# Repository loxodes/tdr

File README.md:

# tdr
Prototype time domain reflectometer/sampling oscilloscope.
90 gigasamples/second equivalent time sampling with an actual sampling rate of 5 kilosamples/second.

The input bandwidth is TBD, maybe 8 GHz?

Following is sampling the falling edge of the TDR pulse, impedance of a BNC tee, and a 1.2 GHz sine wave with analog triggering.

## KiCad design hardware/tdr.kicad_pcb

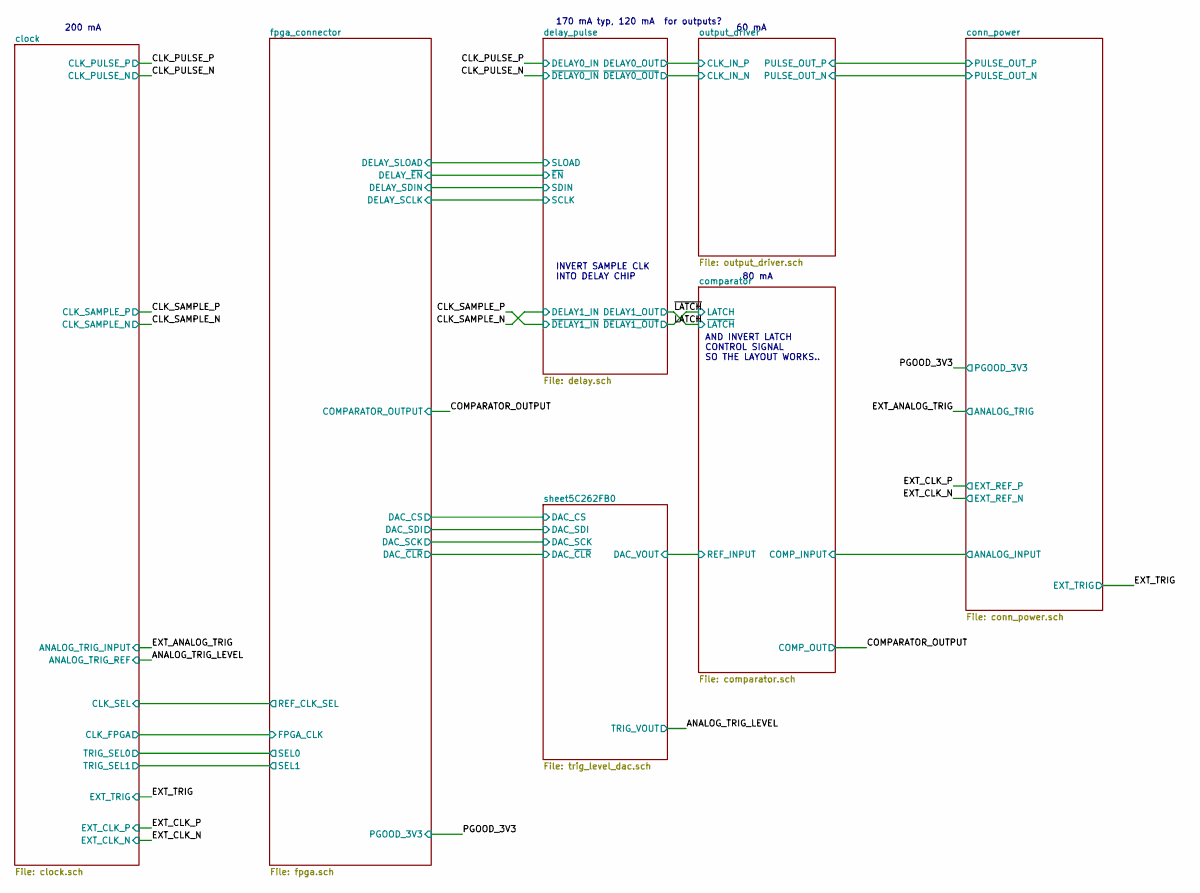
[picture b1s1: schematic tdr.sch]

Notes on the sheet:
200 mA
170 mA typ, 120 mA for outputs?
60 mA
80 mA
INVERT SAMPLE CLK INTO DELAY CHIP
AND INVERT LATCH CONTROL SIGNAL SO THE LAYOUT WORKS..

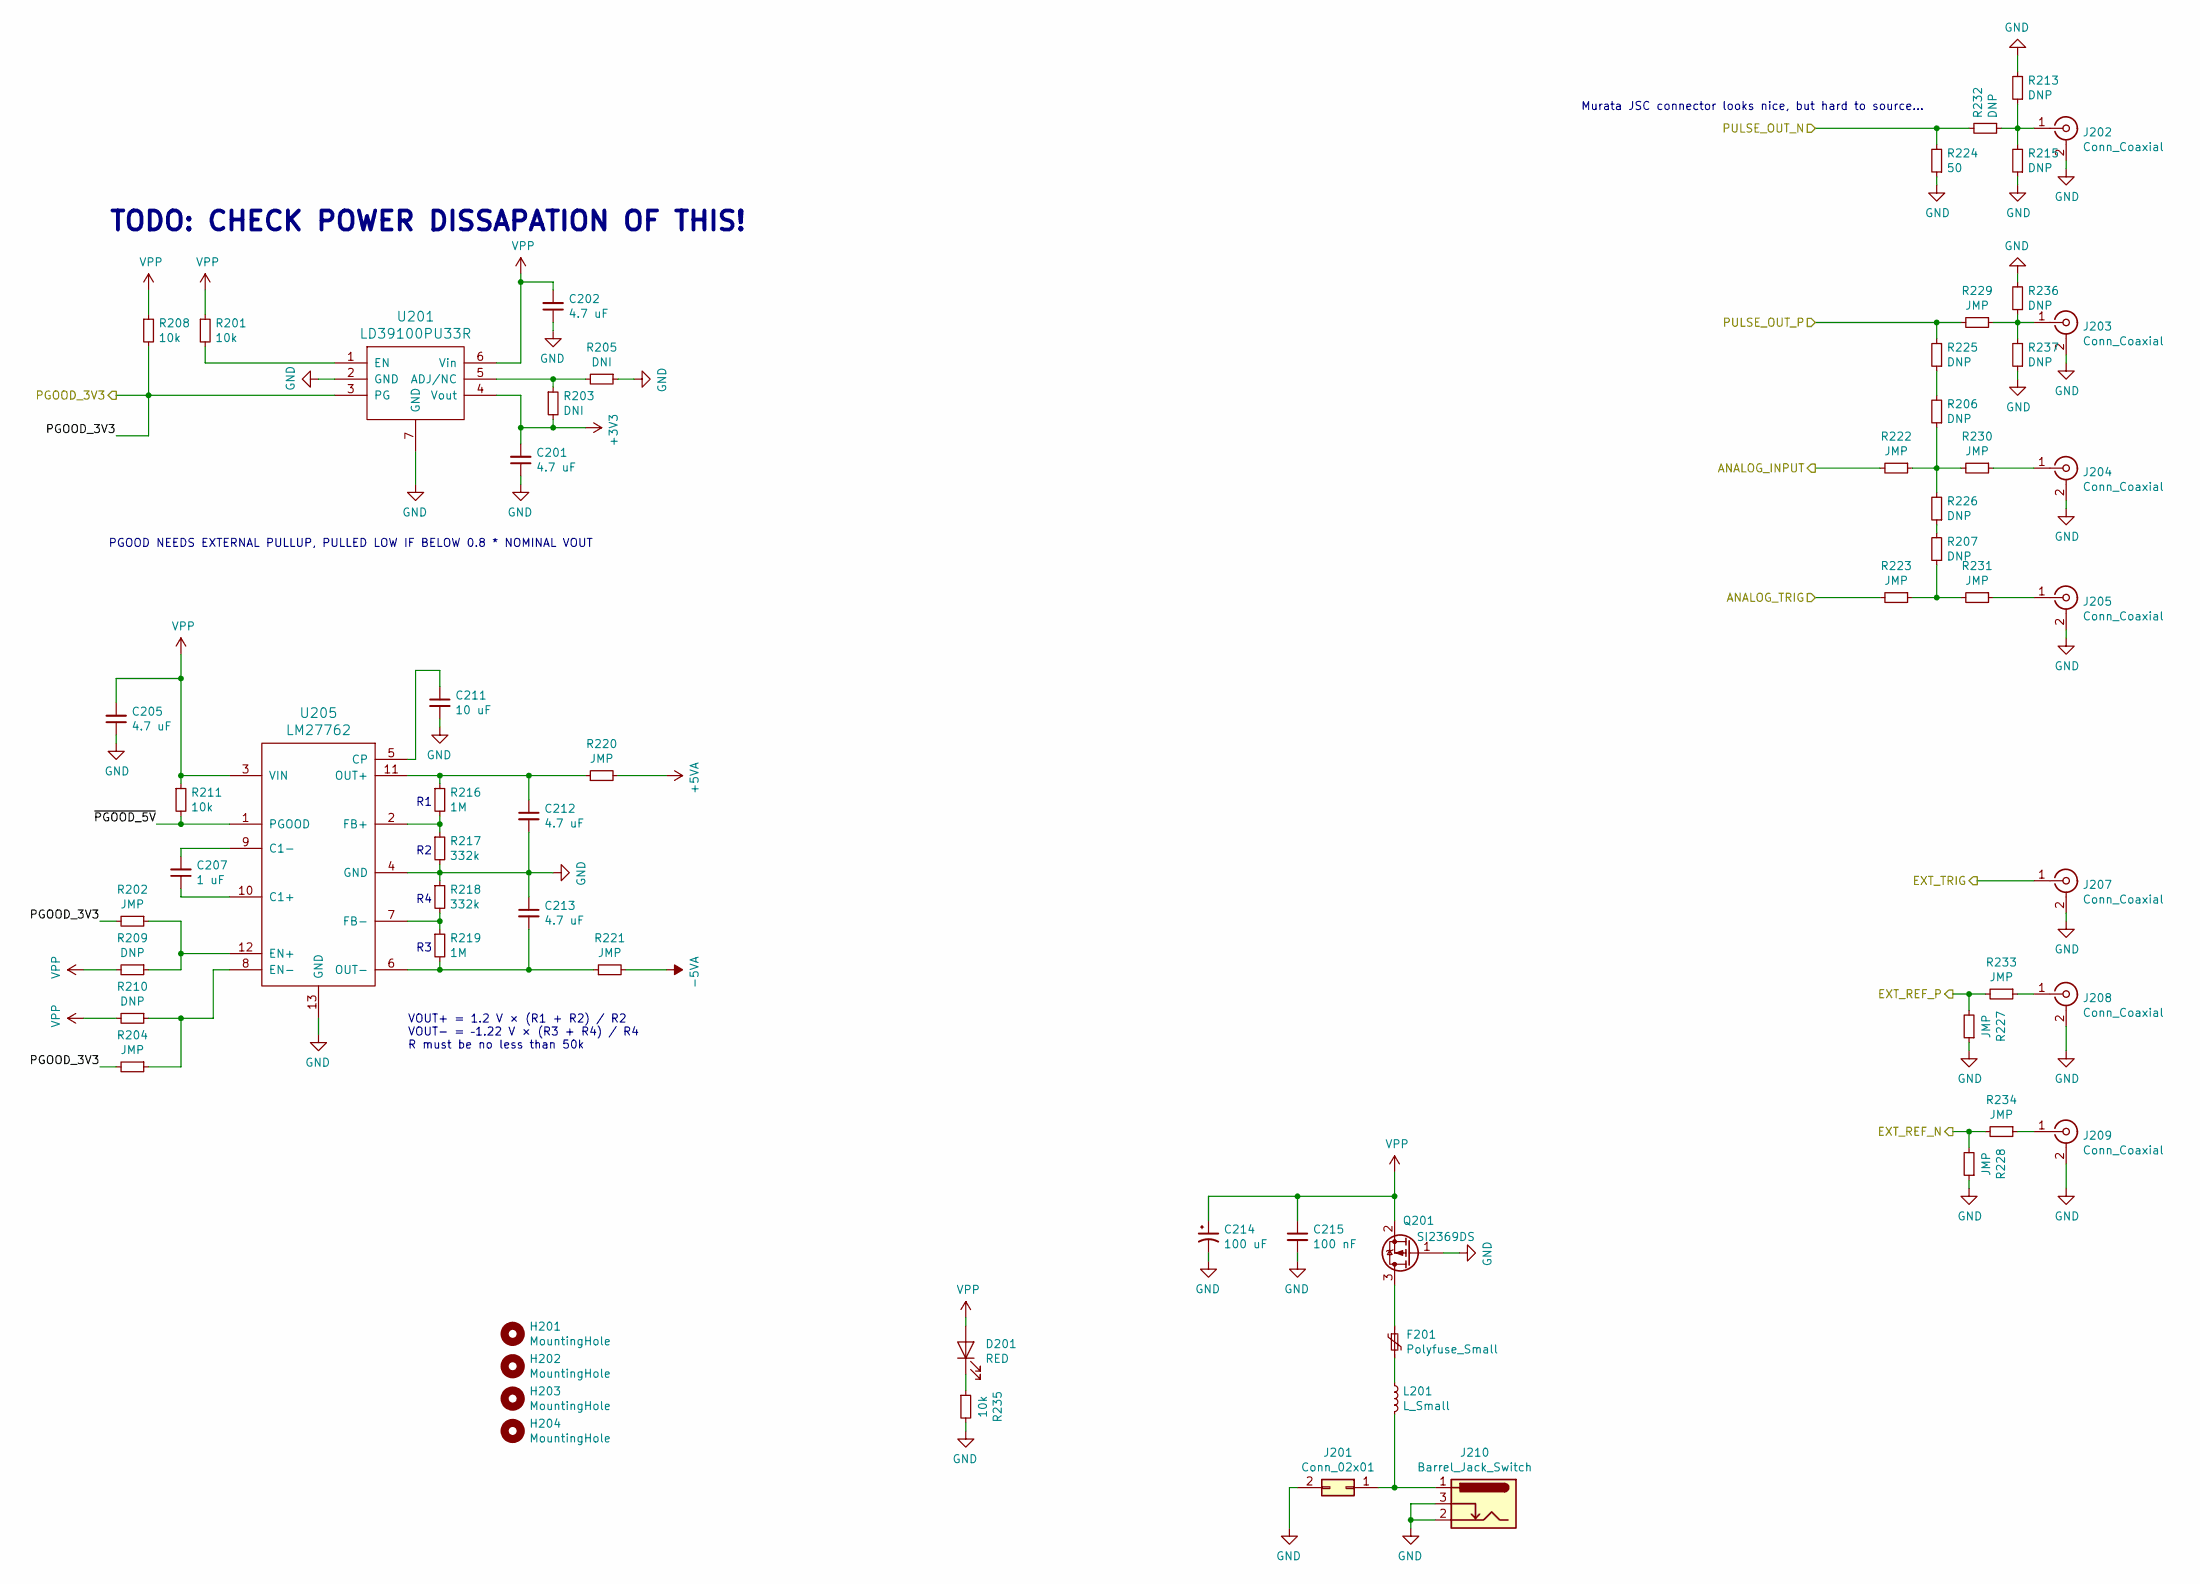
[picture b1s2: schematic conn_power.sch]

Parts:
C201, C202, C205, C212, C213: 4.7 uF; C_0603
C207: 1 uF; C_0402
C211: 10 uF; C_0603
C214: 100 uF; c_elec_6.3x5.8
C215: 100 nF; C_0402
D201: RED; LED_0603
F201: Polyfuse_Small; R_1210
H201, H202, H203, H204: MountingHole; MountingHole_2-5mm
J201: Conn_02x01; TerminalBlock_Pheonix_MPT-2.54mm_2pol
J202: Conn_Coaxial; 734120110_ufl_umc
J203, J204, J205, J207: Conn_Coaxial; SF2921-61345
J208, J209: Conn_Coaxial; 732511150_sma_thin_twopin
J210: Barrel_Jack_Switch; BARREL_JACK
L201: L_Small; R_1210
Q201: SI2369DS; SOT-23
R201, R208, R211, R235: 10k; R_0402
R202, R204, R220, R221, R227, R228, R233, R234: JMP; R_0402
R203, R205: DNI; R_0402
R206, R207, R225, R226, R232: DNP; R_0201
R209, R210, R213, R215, R236, R237: DNP; R_0402
R216, R219: 1M; R_0402
R217, R218: 332k; R_0402
R222, R223, R229, R230, R231: JMP; R_0201
R224: 50; R_0402
U201: LD39100PU33R; DFN-6-1EP_3x3mm_Pitch0.95mm
U205: LM27762; WSON-12-1EP_3x2mm_Pitch0.5mm

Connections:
+3V3: C201.2, R203.2, U201.4 (Vout); also elsewhere on the board
+5VA: R220.2; also elsewhere on the board
-5VA: R221.2; also elsewhere on the board
/EXT_ANALOG_TRIG: R223.2; also elsewhere on the board
/EXT_CLK_N: R228.2, R234.2; also elsewhere on the board
/EXT_CLK_P: R227.2, R233.2; also elsewhere on the board
/EXT_TRIG: J207.1 (In); also elsewhere on the board
/PGOOD_3V3: R202.2, R204.2, R208.2, U201.3 (PG); also elsewhere on the board
/conn_power/ANALOG_INPUT: R222.2; also elsewhere on the board
/conn_power/PULSE_OUT_N: R224.2, R232.2; also elsewhere on the board
/conn_power/PULSE_OUT_P: R225.2, R229.2; also elsewhere on the board
/conn_power/~PGOOD_5V: R211.2, U205.1 (PGOOD)
GND: C201.1, C202.1, C205.1, C211.2, C212.2, C213.1, C214.2, C215.2, J201.2, J202.2 (Ext), J203.2 (Ext), J204.2 (Ext), J205.2 (Ext), J207.2 (Ext), J208.2 (Ext), J209.2 (Ext), J210.2, J210.3, Q201.1 (G), R205.1, R213.2, R215.1, R217.2, R218.1, R224.1, R227.1, R228.1, R235.2, R236.2, R237.1, U201.2 (GND), U201.7 (GND), U205.4 (GND), U205.13 (GND); also elsewhere on the board
unnamed: C207.1, U205.10 (C1+)
unnamed: C207.2, U205.9 (C1-)
unnamed: C211.1, U205.5 (CP)
unnamed: C212.1, R216.1, R220.1, U205.11 (OUT+)
unnamed: C213.2, R219.2, R221.1, U205.6 (OUT-)
unnamed: D201.1 (K), R235.1
unnamed: F201.1, Q201.3 (D)
unnamed: F201.2, L201.1
unnamed: J201.1, J210.1, L201.2
unnamed: J202.1 (In), R213.1, R215.2, R232.1
unnamed: J203.1 (In), R229.1, R236.1, R237.2
unnamed: J204.1 (In), R230.1
unnamed: J205.1 (In), R231.1
unnamed: J208.1 (In), R233.1
unnamed: J209.1 (In), R234.1
unnamed: R201.2, U201.1 (EN)
unnamed: R202.1, R209.1, U205.12 (EN+)
unnamed: R203.1, R205.2, U201.5 (ADJ/NC)
unnamed: R204.1, R210.1, U205.8 (EN-)
unnamed: R206.1, R222.1, R226.2, R230.2
unnamed: R206.2, R225.1
unnamed: R207.1, R223.1, R231.2
unnamed: R207.2, R226.1
unnamed: R216.2, R217.1, U205.2 (FB+)
unnamed: R218.2, R219.1, U205.7 (FB-)
VPP: C202.2, C205.2, C214.1, C215.1, D201.2 (A), Q201.2 (S), R201.1, R208.1, R209.2, R210.2, R211.1, U201.6 (Vin), U205.3 (VIN)

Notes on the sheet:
PGOOD NEEDS EXTERNAL PULLUP, PULLED LOW IF BELOW 0.8 * NOMINAL VOUT
TODO: CHECK POWER DISSAPATION OF THIS!
Murata JSC connector looks nice, but hard to source...
VOUT+ = 1.2 V × (R1 + R2) / R2 VOUT- = –1.22 V × (R3 + R4) / R4 R must be no less than 50k

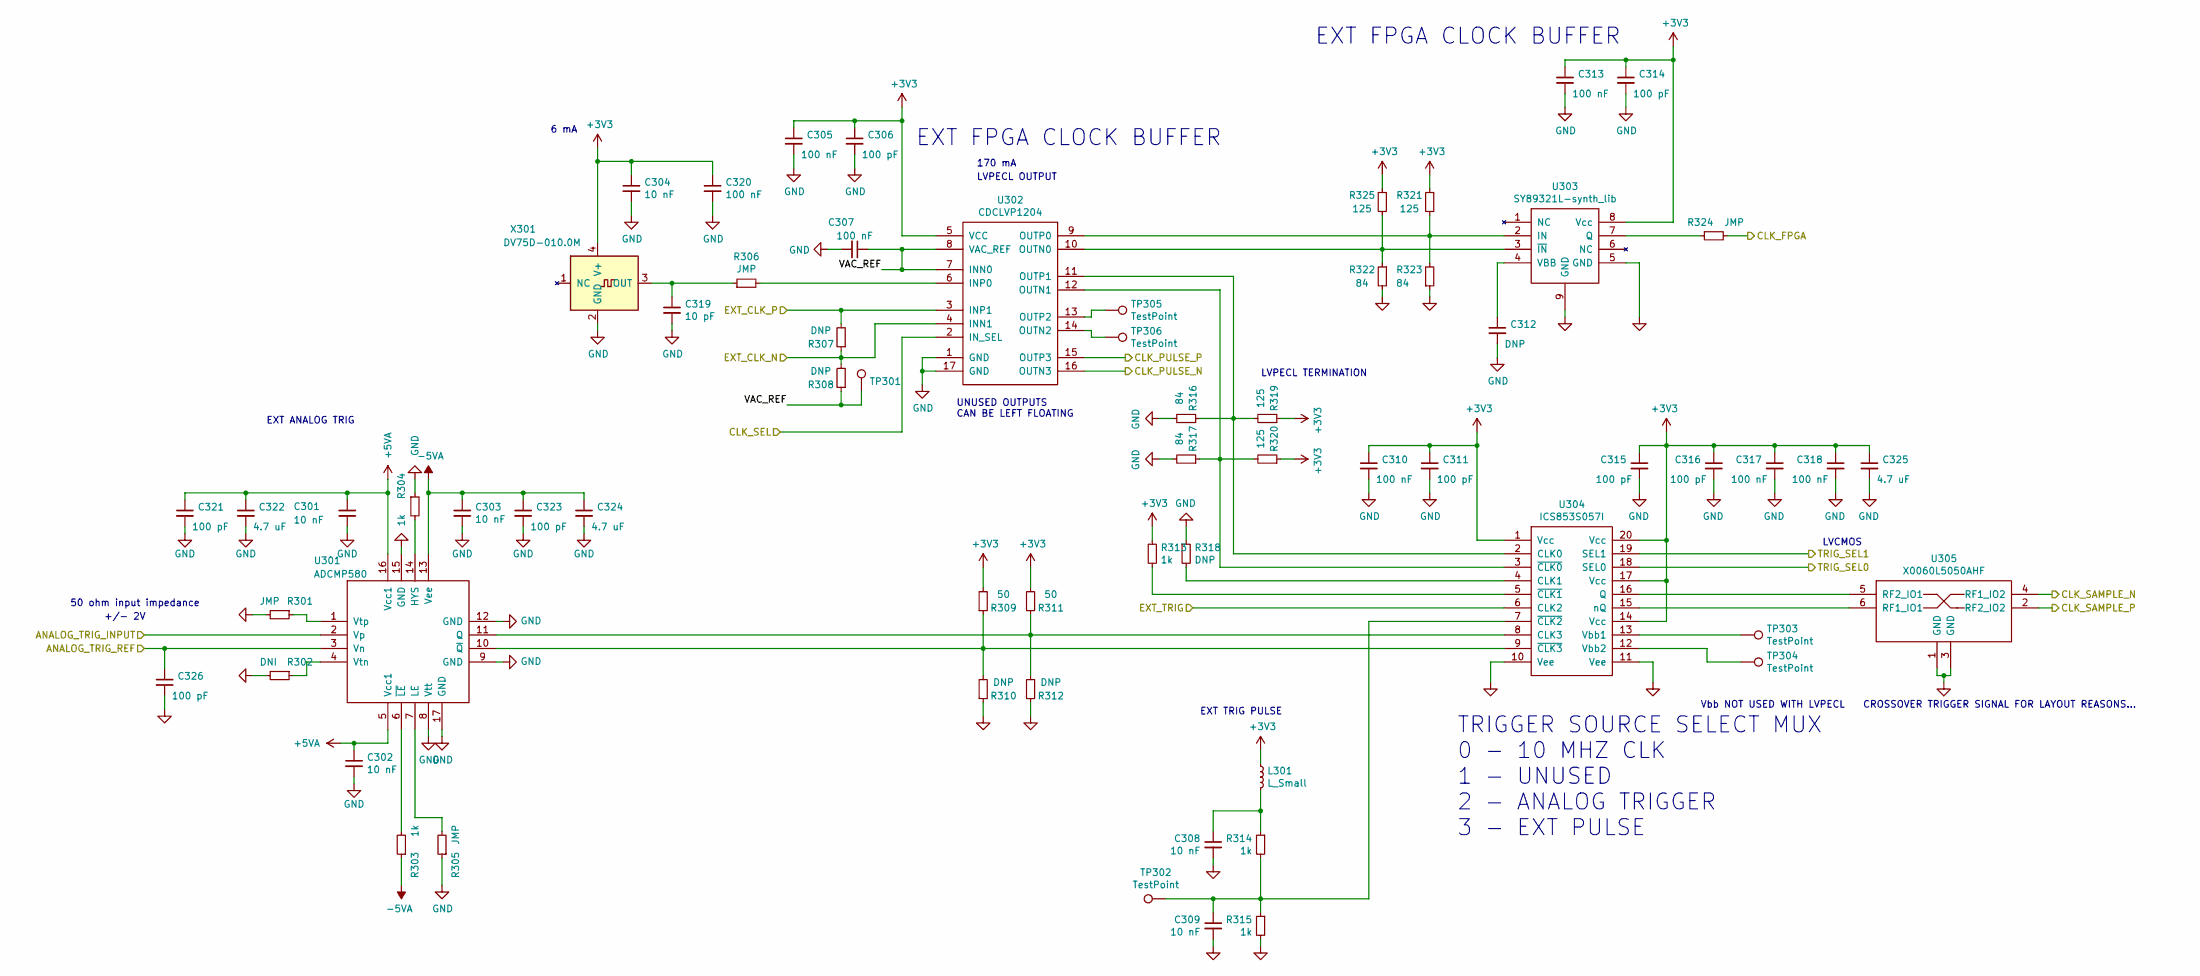
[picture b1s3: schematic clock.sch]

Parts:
C301, C302, C303, C304, C308, C309: 10 nF; C_0402
C305, C307, C310, C313, C317, C318, C320: 100 nF; C_0402
C306, C311, C314, C315, C316, C321, C323, C326: 100 pF; C_0402
C312: DNP; C_0402
C319: 10 pF; C_0402
C322, C324, C325: 4.7 uF; C_0603
L301: L_Small; R_0402
R301, R305, R306, R324: JMP; R_0402
R302: DNI; R_0402
R303, R304, R313, R314, R315: 1k; R_0402
R307, R308, R310, R312, R318: DNP; R_0402
R309, R311: 50; R_0402
R316, R317, R322, R323: 84; R_0402
R319, R320, R321, R325: 125; R_0402
TP301, TP302, TP303, TP304, TP305, TP306: TestPoint; TP07R
U301: ADCMP580; UQFN-16-1EP_3x3mm_Pitch0.5mm
U302: CDCLVP1204; UQFN-16-1EP_3x3mm_Pitch0.5mm
U303: SY89321L-synth_lib; DFN-8-1EP_2x2mm_Pitch0.5mm
U304: ICS853S057I; TSSOP-20_4.4x6.5mm_Pitch0.65mm
U305: X0060L5050AHF
X301: DV75D-010.0M; DV75D

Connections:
+3V3: C304.1, C305.1, C306.1, C310.1, C311.1, C313.1, C314.1, C315.1, C316.1, C317.1, C318.1, C320.1, C325.1, L301.1, R309.2, R311.2, R313.1, R319.1, R320.1, R321.1, R325.1, U302.5 (VCC), U303.8 (Vcc), U304.1 (Vcc), U304.14 (Vcc), U304.17 (Vcc), U304.20 (Vcc), X301.4 (V+); also elsewhere on the board
+5VA: C301.1, C302.1, C321.1, C322.1, U301.5 (Vcc1), U301.16 (Vcc1); also elsewhere on the board
-5VA: C303.1, C323.1, C324.1, R303.1, U301.13 (Vee); also elsewhere on the board
/ANALOG_TRIG_LEVEL: C326.1, U301.3 (Vn); also elsewhere on the board
/CLK_PULSE_N: U302.16 (OUTN3); also elsewhere on the board
/CLK_PULSE_P: U302.15 (OUTP3); also elsewhere on the board
/CLK_SAMPLE_N: U305.4 (RF1_IO2); also elsewhere on the board
/CLK_SAMPLE_P: U305.2 (RF2_IO2); also elsewhere on the board
/EXT_ANALOG_TRIG: U301.2 (Vp); also elsewhere on the board
/EXT_CLK_N: R307.1, R308.2, U302.4 (INN1); also elsewhere on the board
/EXT_CLK_P: R307.2, U302.3 (INP1); also elsewhere on the board
/EXT_TRIG: U304.6 (CLK2); also elsewhere on the board
/clock/CLK_FPGA: R324.2; also elsewhere on the board
/clock/CLK_SEL: U302.2 (IN_SEL); also elsewhere on the board
/clock/VAC_REF: C307.1, R308.1, TP301.1, U302.7 (INN0), U302.8 (VAC_REF)
/fpga_connector/SEL0: U304.18 (SEL0); also elsewhere on the board
/fpga_connector/SEL1: U304.19 (SEL1); also elsewhere on the board
GND: C301.2, C302.2, C303.2, C304.2, C305.2, C306.2, C307.2, C308.2, C309.2, C310.2, C311.2, C312.2, C313.2, C314.2, C315.2, C316.2, C317.2, C318.2, C319.2, C320.2, C321.2, C322.2, C323.2, C324.2, C325.2, C326.2, R301.2, R302.2, R304.1, R305.1, R310.1, R312.1, R315.2, R316.2, R317.2, R318.1, R322.2, R323.1, U301.8 (Vtt), U301.9 (GND), U301.12 (GND), U301.15 (GND), U301.17 (GND), U302.1 (GND), U302.17 (GND), U303.5 (GND), U303.9 (GND), U304.10 (Vee), U304.11 (Vee), U305.1 (GND), U305.3 (GND), X301.2 (GND); also elsewhere on the board
unnamed: C308.1, L301.2, R314.1
unnamed: C309.1, R314.2, R315.1, TP302.1, U304.7 (~CLK2)
unnamed: C312.1, U303.4 (VBB)
unnamed: C319.1, R306.1, X301.3 (OUT)
unnamed: R301.1, U301.1 (Vtp)
unnamed: R302.1, U301.4 (Vtn)
unnamed: R303.2, U301.6 (~LE)
unnamed: R304.2, U301.14 (HYS)
unnamed: R305.2, U301.7 (LE)
unnamed: R306.2, U302.6 (INP0)
unnamed: R309.1, R310.2, U301.10 (~Q), U304.9 (~CLK3)
unnamed: R311.1, R312.2, U301.11 (Q), U304.8 (CLK3)
unnamed: R313.2, U304.5 (~CLK1)
unnamed: R316.1, R319.2, U302.11 (OUTP1), U304.2 (CLK0)
unnamed: R317.1, R320.2, U302.12 (OUTN1), U304.3 (~CLK0)
unnamed: R318.2, U304.4 (CLK1)
unnamed: R321.2, R323.2, U302.9 (OUTP0), U303.2 (IN)
unnamed: R322.1, R325.2, U302.10 (OUTN0), U303.3 (~IN)
unnamed: R324.1, U303.7 (Q)
unnamed: TP303.1, U304.13 (Vbb1)
unnamed: TP304.1, U304.12 (Vbb2)
unnamed: TP305.1, U302.13 (OUTP2)
unnamed: TP306.1, U302.14 (OUTN2)
unnamed: U304.15 (nQ), U305.6 (RF1_IO1)
unnamed: U304.16 (Q), U305.5 (RF2_IO1)

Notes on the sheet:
6 mA
170 mA
LVPECL OUTPUT
EXT ANALOG TRIG
LVPECL TERMINATION
+/- 2V
EXT TRIG PULSE
50 ohm input impedance
LVCMOS
Vbb NOT USED WITH LVPECL
TRIGGER SOURCE SELECT MUX 0 - 10 MHZ CLK 1 - UNUSED 2 - ANALOG TRIGGER 3 - EXT PULSE
EXT FPGA CLOCK BUFFER
UNUSED OUTPUTS CAN BE LEFT FLOATING
CROSSOVER TRIGGER SIGNAL FOR LAYOUT REASONS...

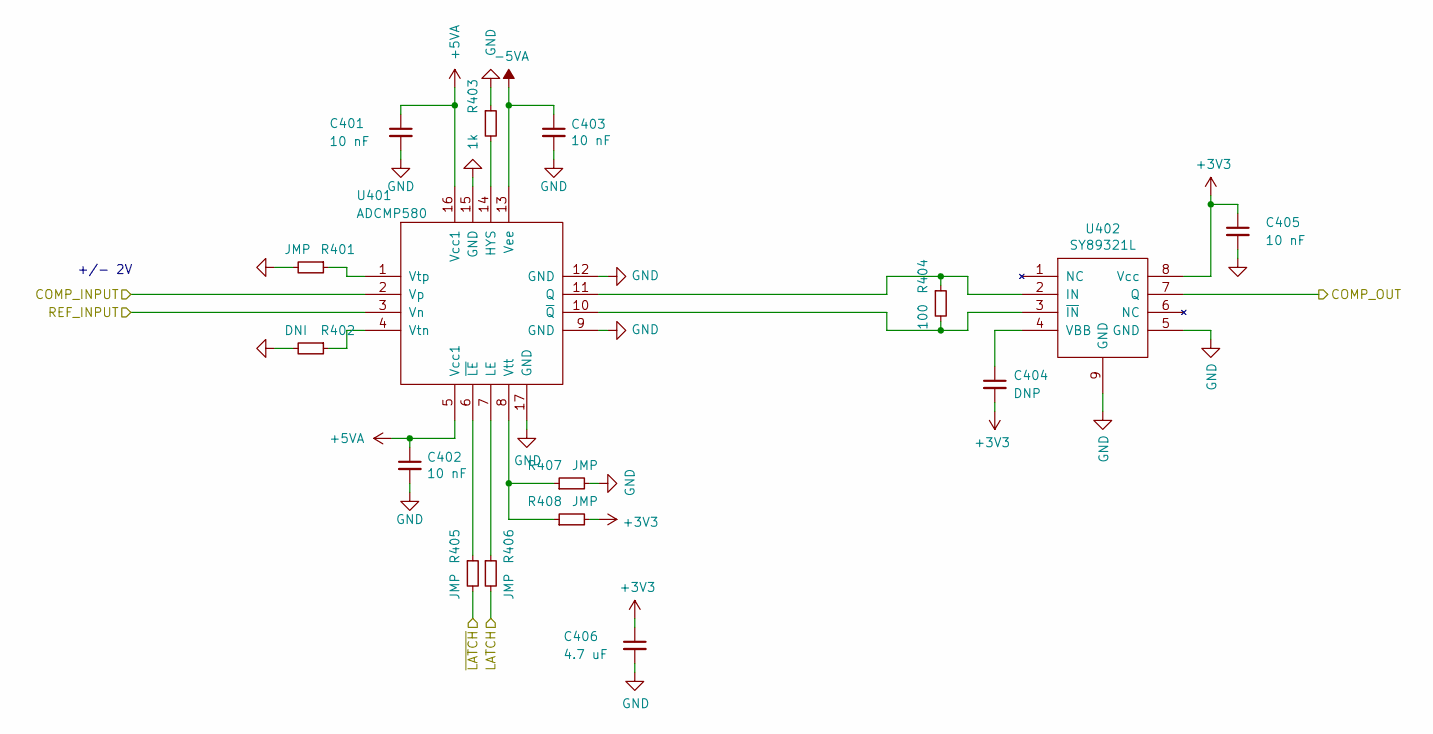
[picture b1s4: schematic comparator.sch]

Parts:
C401, C402, C403, C405: 10 nF; C_0402
C404: DNP; C_0402
C406: 4.7 uF; C_0603
R401, R405, R406, R407, R408: JMP; R_0402
R402: DNI; R_0402
R403: 1k; R_0402
R404: 100; R_0402
U401: ADCMP580; QFN-16-1EP_3x3mm_Pitch0.5mm
U402: SY89321L; DFN-8-1EP_2x2mm_Pitch0.5mm

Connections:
+3V3: C404.2, C405.1, C406.1, R408.2, U402.8 (Vcc); also elsewhere on the board
+5VA: C401.1, C402.1, U401.5 (Vcc1), U401.16 (Vcc1); also elsewhere on the board
-5VA: C403.1, U401.13 (Vee); also elsewhere on the board
/COMPARATOR_OUTPUT: U402.7 (Q); also elsewhere on the board
/LATCH: R406.2; also elsewhere on the board
/conn_power/ANALOG_INPUT: U401.2 (Vp); also elsewhere on the board
/sheet5C262FB0/DAC_VOUT: U401.3 (Vn); also elsewhere on the board
/~LATCH: R405.2; also elsewhere on the board
GND: C401.2, C402.2, C403.2, C405.2, C406.2, R401.2, R402.2, R403.1, R407.2, U401.9 (GND), U401.12 (GND), U401.15 (GND), U401.17 (GND), U402.5 (GND), U402.9 (GND); also elsewhere on the board
unnamed: C404.1, U402.4 (VBB)
unnamed: R401.1, U401.1 (Vtp)
unnamed: R402.1, U401.4 (Vtn)
unnamed: R403.2, U401.14 (HYS)
unnamed: R404.1, U401.11 (Q), U402.2 (IN)
unnamed: R404.2, U401.10 (~Q), U402.3 (~IN)
unnamed: R405.1, U401.6 (~LE)
unnamed: R406.1, U401.7 (LE)
unnamed: R407.1, R408.1, U401.8 (Vtt)

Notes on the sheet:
+/- 2V

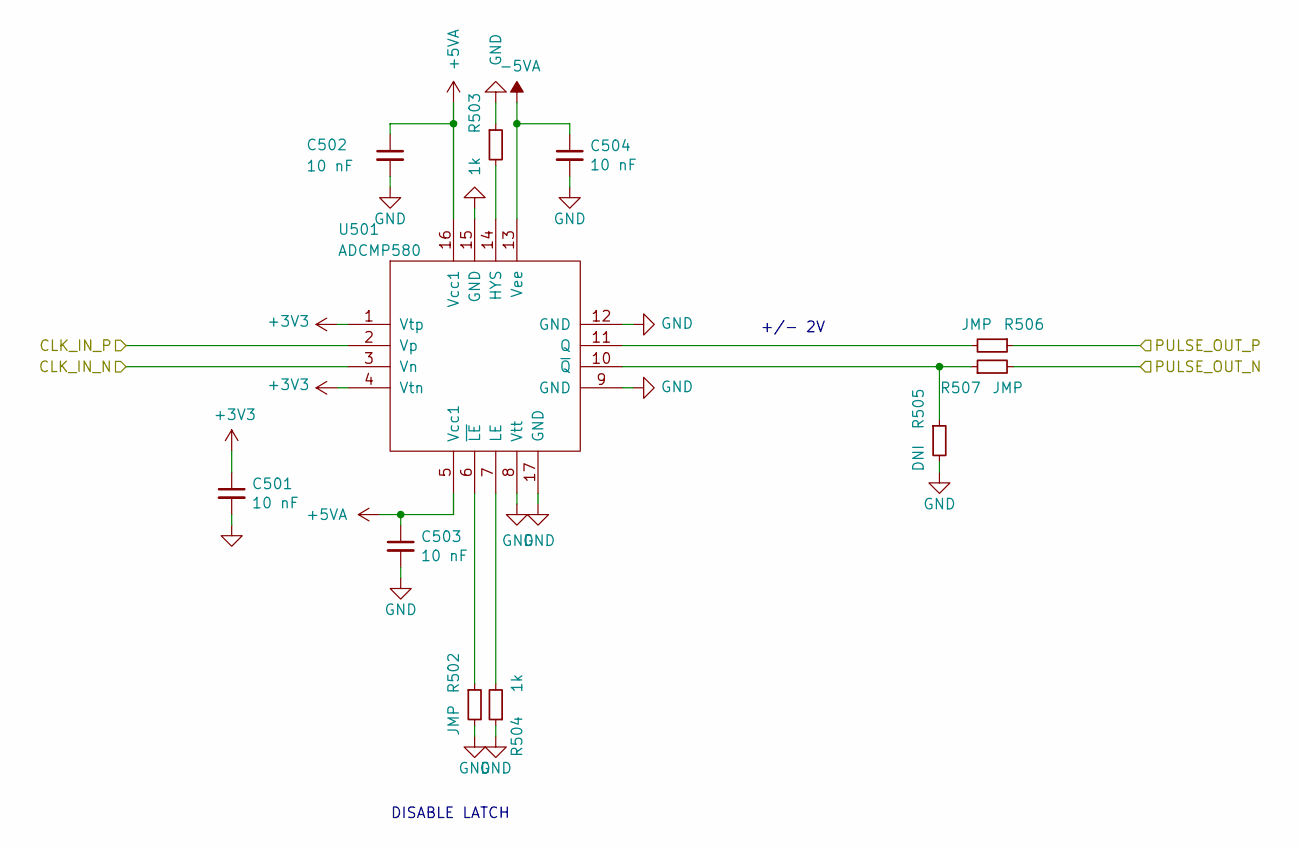
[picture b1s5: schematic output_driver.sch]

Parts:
C501, C502, C503, C504: 10 nF; C_0402
R502: JMP; R_0402
R503, R504: 1k; R_0402
R505: DNI; R_0402
R506, R507: JMP; R_0201
U501: ADCMP580; QFN-16-1EP_3x3mm_Pitch0.5mm

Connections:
+3V3: C501.1, U501.1 (Vtp), U501.4 (Vtn); also elsewhere on the board
+5VA: C502.1, C503.1, U501.5 (Vcc1), U501.16 (Vcc1); also elsewhere on the board
-5VA: C504.1, U501.13 (Vee); also elsewhere on the board
/conn_power/PULSE_OUT_N: R507.2; also elsewhere on the board
/conn_power/PULSE_OUT_P: R506.1; also elsewhere on the board
/output_driver/CLK_IN_N: U501.3 (Vn); also elsewhere on the board
/output_driver/CLK_IN_P: U501.2 (Vp); also elsewhere on the board
GND: C501.2, C502.2, C503.2, C504.2, R502.2, R503.1, R504.1, R505.2, U501.8 (Vtt), U501.9 (GND), U501.12 (GND), U501.15 (GND), U501.17 (GND); also elsewhere on the board
unnamed: R502.1, U501.6 (~LE)
unnamed: R503.2, U501.14 (HYS)
unnamed: R504.2, U501.7 (LE)
unnamed: R505.1, R507.1, U501.10 (~Q)
unnamed: R506.2, U501.11 (Q)

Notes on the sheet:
+/- 2V
DISABLE LATCH

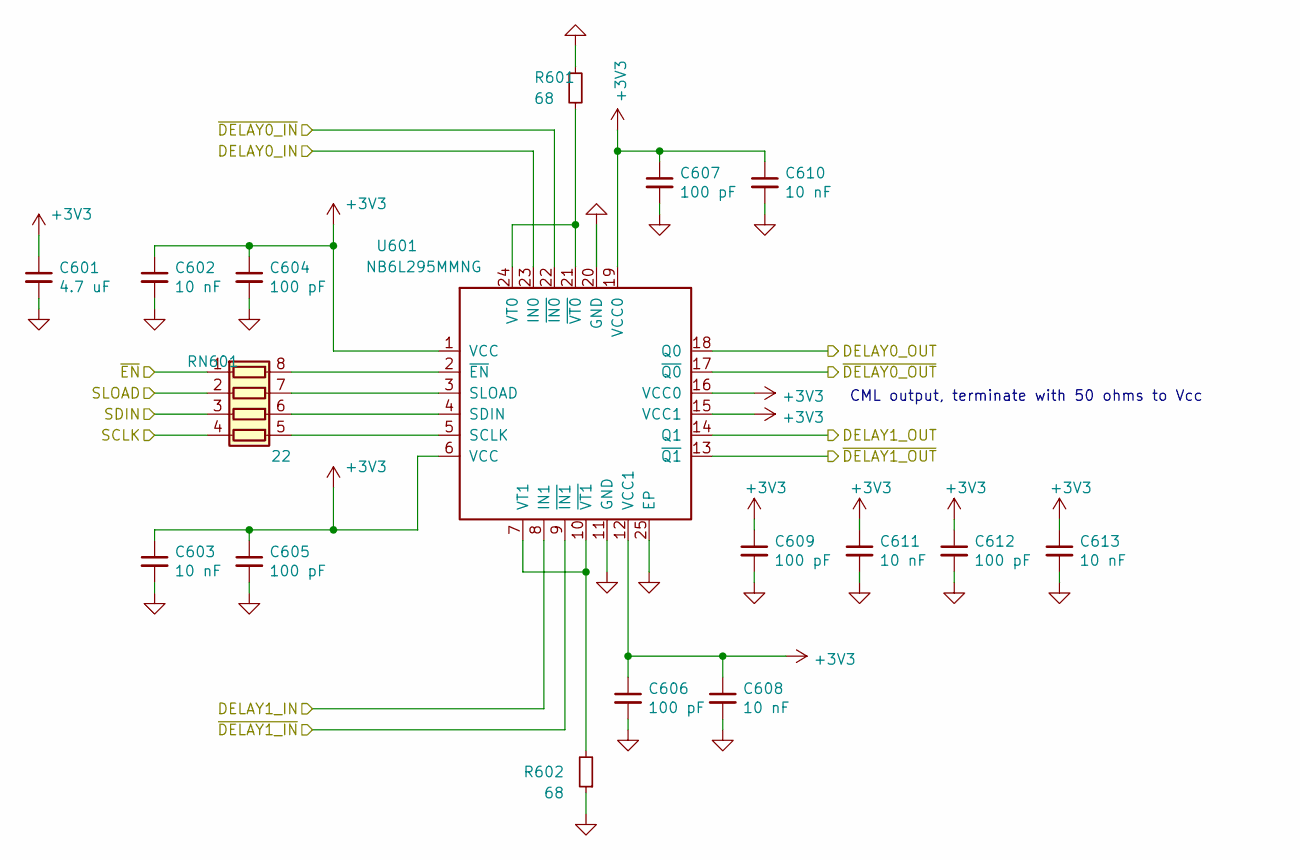
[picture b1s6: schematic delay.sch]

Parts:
C601: 4.7 uF; C_0603
C602, C603, C608, C610, C611, C613: 10 nF; C_0402
C604, C605, C606, C607, C609, C612: 100 pF; C_0402
R601, R602: 68; R_0402
RN601: 22; R_Array_Convex_4x0402
U601: NB6L295MMNG; QFN-24-1EP_4x4mm_Pitch0.5mm

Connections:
+3V3: C601.1, C602.1, C603.1, C604.1, C605.1, C606.1, C607.1, C608.1, C609.1, C610.1, C611.1, C612.1, C613.1, U601.1 (VCC), U601.6 (VCC), U601.12 (VCC1), U601.15 (VCC1), U601.16 (VCC0), U601.19 (VCC0); also elsewhere on the board
/CLK_PULSE_N: U601.22 (~IN0); also elsewhere on the board
/CLK_PULSE_P: U601.23 (IN0); also elsewhere on the board
/CLK_SAMPLE_N: U601.8 (IN1); also elsewhere on the board
/CLK_SAMPLE_P: U601.9 (~IN1); also elsewhere on the board
/LATCH: U601.13 (~Q1); also elsewhere on the board
/fpga_connector/DELAY_SCLK: RN601.4 (R4.1); also elsewhere on the board
/fpga_connector/DELAY_SDIN: RN601.3 (R3.1); also elsewhere on the board
/fpga_connector/DELAY_SLOAD: RN601.2 (R2.1); also elsewhere on the board
/fpga_connector/DELAY_~EN: RN601.1 (R1.1); also elsewhere on the board
/output_driver/CLK_IN_N: U601.17 (~Q0); also elsewhere on the board
/output_driver/CLK_IN_P: U601.18 (Q0); also elsewhere on the board
/~LATCH: U601.14 (Q1); also elsewhere on the board
GND: C601.2, C602.2, C603.2, C604.2, C605.2, C606.2, C607.2, C608.2, C609.2, C610.2, C611.2, C612.2, C613.2, R601.1, R602.1, U601.11 (GND), U601.20 (GND), U601.25 (EP); also elsewhere on the board
unnamed: R601.2, U601.21 (~VT0), U601.24 (VT0)
unnamed: R602.2, U601.7 (VT1), U601.10 (~VT1)
unnamed: RN601.5 (R4.2), U601.5 (SCLK)
unnamed: RN601.6 (R3.2), U601.4 (SDIN)
unnamed: RN601.7 (R2.2), U601.3 (SLOAD)
unnamed: RN601.8 (R1.2), U601.2 (~EN)

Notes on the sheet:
CML output, terminate with 50 ohms to Vcc

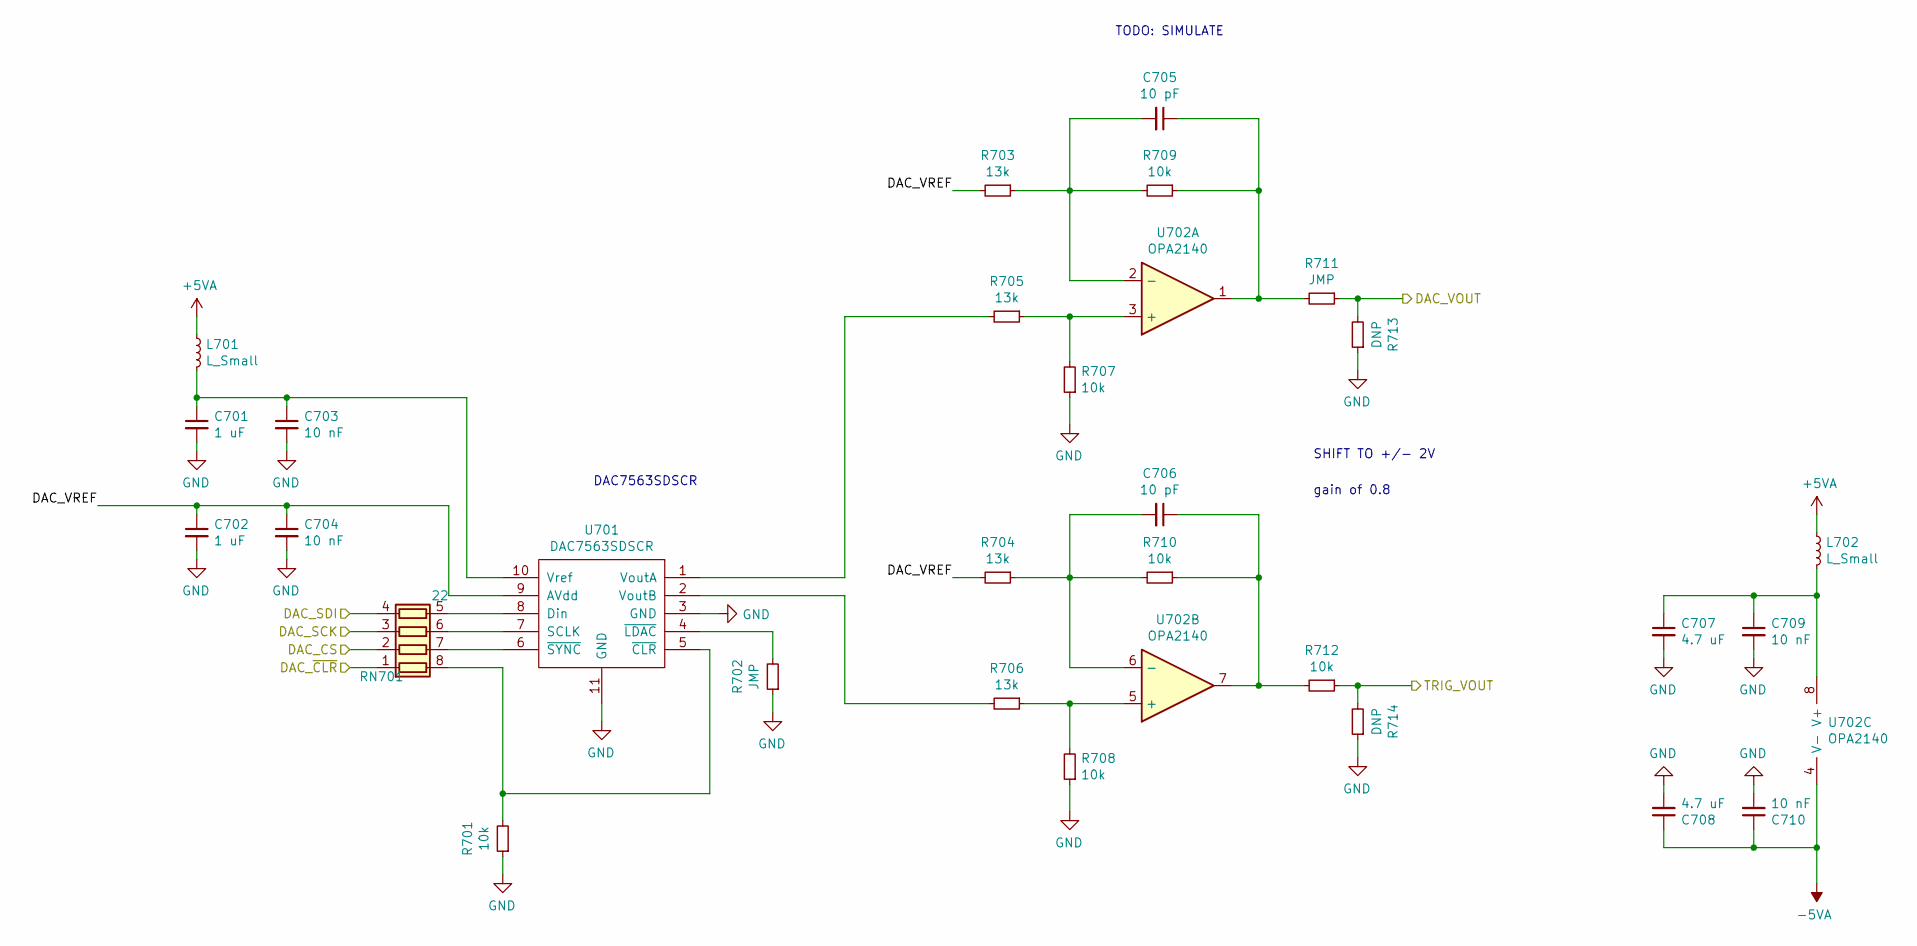
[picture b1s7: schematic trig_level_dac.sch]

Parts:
C701, C702: 1 uF; C_0402
C703, C704, C709, C710: 10 nF; C_0402
C705, C706: 10 pF; C_0402
C707, C708: 4.7 uF; C_0603
L701, L702: L_Small; R_0402
R701, R707, R708, R709, R710, R712: 10k; R_0402
R702, R711: JMP; R_0402
R703, R704, R705, R706: 13k; R_0402
R713, R714: DNP; R_0402
RN701: 22; R_Array_Convex_4x0402
U701: DAC7563SDSCR; DFN-10-1EP_3x3mm_Pitch0.5mm
U702: OPA2140; MSOP-8_3x3mm_Pitch0.65mm

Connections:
+5VA: L701.1, L702.1; also elsewhere on the board
-5VA: C708.1, C710.1, U702.4 (V-); also elsewhere on the board
/ANALOG_TRIG_LEVEL: R712.1, R714.2; also elsewhere on the board
/fpga_connector/DAC_CS: RN701.2 (R2.1); also elsewhere on the board
/fpga_connector/DAC_SCK: RN701.3 (R3.1); also elsewhere on the board
/fpga_connector/DAC_SDI: RN701.4 (R4.1); also elsewhere on the board
/fpga_connector/DAC_~CLR: RN701.1 (R1.1); also elsewhere on the board
/sheet5C262FB0/DAC_VOUT: R711.1, R713.2; also elsewhere on the board
/sheet5C262FB0/DAC_VREF: C702.1, C704.1, R703.2, R704.2, U701.9 (AVdd)
GND: C701.2, C702.2, C703.2, C704.2, C707.2, C708.2, C709.2, C710.2, R701.1, R702.1, R707.1, R708.1, R713.1, R714.1, U701.3 (GND), U701.11 (GND); also elsewhere on the board
unnamed: C701.1, C703.1, L701.2, U701.10 (Vref)
unnamed: C705.1, R709.1, R711.2, U702.1
unnamed: C705.2, R703.1, R709.2, U702.2 (-)
unnamed: C706.1, R710.1, R712.2, U702.7
unnamed: C706.2, R704.1, R710.2, U702.6 (-)
unnamed: C707.1, C709.1, L702.2, U702.8 (V+)
unnamed: R701.2, RN701.8 (R1.2), U701.5 (~CLR)
unnamed: R702.2, U701.4 (~LDAC)
unnamed: R705.1, R707.2, U702.3 (+)
unnamed: R705.2, U701.1 (VoutA)
unnamed: R706.1, R708.2, U702.5 (+)
unnamed: R706.2, U701.2 (VoutB)
unnamed: RN701.5 (R4.2), U701.8 (Din)
unnamed: RN701.6 (R3.2), U701.7 (SCLK)
unnamed: RN701.7 (R2.2), U701.6 (~SYNC)

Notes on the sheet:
DAC7563SDSCR
SHIFT TO +/- 2V
gain of 0.8
TODO: SIMULATE

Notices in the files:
gateware/tdr.py:
mit license
